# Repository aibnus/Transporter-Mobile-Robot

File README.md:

# Transporter-Mobile-Robot
Mobile Robot with ability to do Line Following, Wall Following, and Transporting any type of object with maximum diameter of 5cm.

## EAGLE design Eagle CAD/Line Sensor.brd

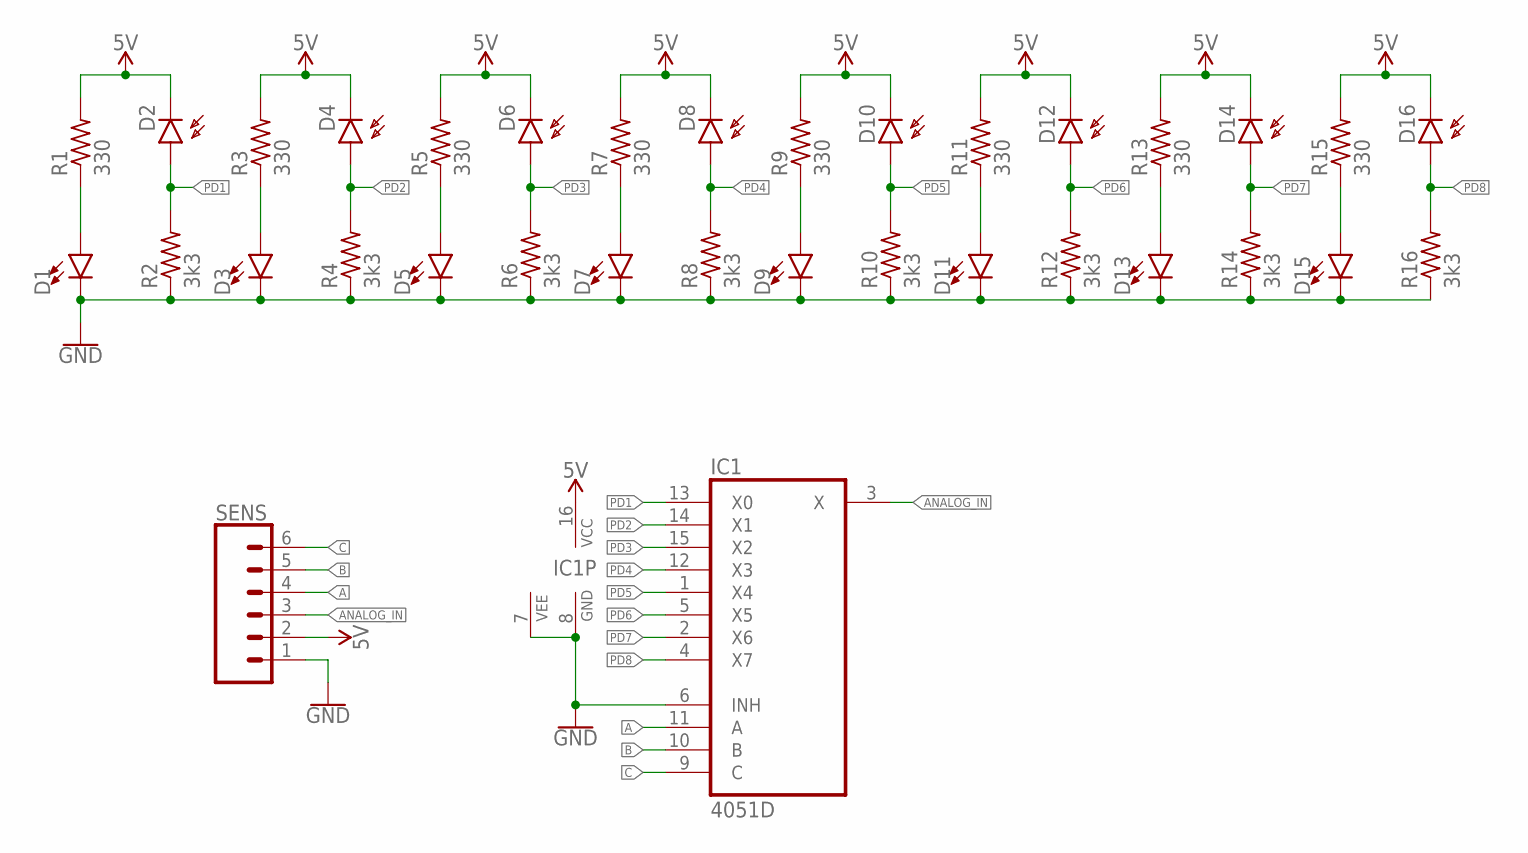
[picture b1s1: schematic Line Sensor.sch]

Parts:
D1, D3, D5, D7, D9, D11, D13, D15: LED3MM; LED_3MM
D2, D4, D6, D8, D10, D12, D14, D16: SFH225
IC1: 4051D; SO16
R1, R3, R5, R7, R9, R11, R13, R15: 330; 0207/9
R2, R4, R6, R8, R10, R12, R14, R16: 3k3; 0207/9
SENS: CONN_06SILK_FEMALE_PTH; 1X06

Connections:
5V: D2.K (C), D4.K (C), D6.K (C), D8.K (C), D10.K (C), D12.K (C), D14.K (C), D16.K (C), IC1.16 (VCC), R1.2, R3.2, R5.2, R7.2, R9.2, R11.2, R13.2, R15.2, SENS.2
A: IC1.11 (A), SENS.4
ANALOG_IN: IC1.3 (X), SENS.3
B: IC1.10 (B), SENS.5
C: IC1.9 (C), SENS.6
GND: D1.K (C), D3.K (C), D5.K (C), D7.K (C), D9.K (C), D11.K (C), D13.K (C), D15.K (C), IC1.6 (INH), IC1.7 (VEE), IC1.8 (GND), R2.1, R4.1, R6.1, R8.1, R10.1, R12.1, R14.1, R16.1, SENS.1
unnamed: D15.A, R15.1
unnamed: D13.A, R13.1
unnamed: D11.A, R11.1
unnamed: D9.A, R9.1
unnamed: D7.A, R7.1
unnamed: D5.A, R5.1
unnamed: D3.A, R3.1
unnamed: D1.A, R1.1
PD1: D2.A, IC1.13 (X0), R2.2
PD2: D4.A, IC1.14 (X1), R4.2
PD3: D6.A, IC1.15 (X2), R6.2
PD4: D8.A, IC1.12 (X3), R8.2
PD5: D10.A, IC1.1 (X4), R10.2
PD6: D12.A, IC1.5 (X5), R12.2
PD7: D14.A, IC1.2 (X6), R14.2
PD8: D16.A, IC1.4 (X7), R16.2

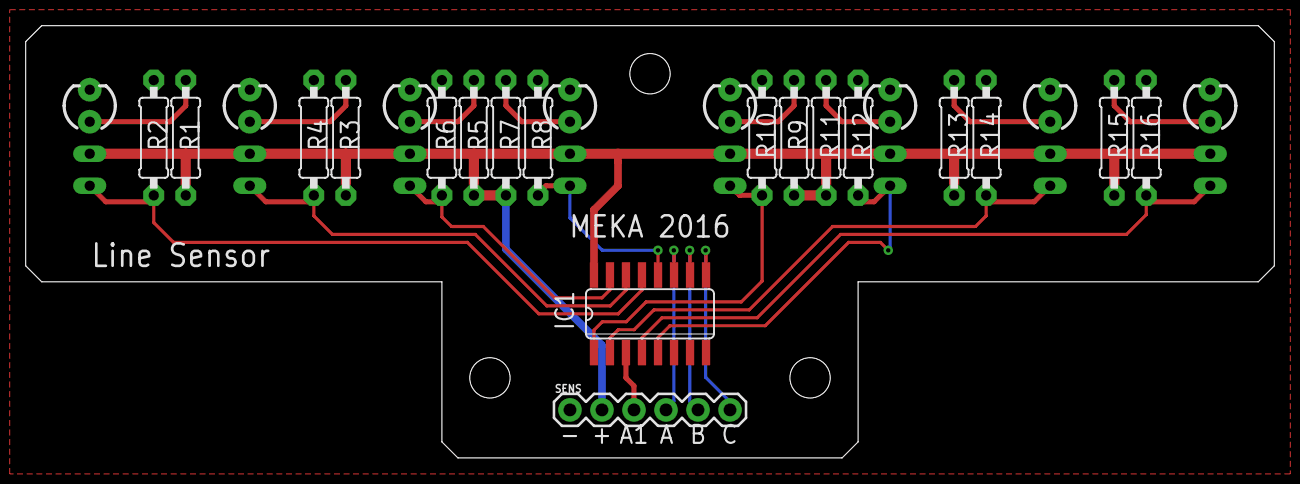
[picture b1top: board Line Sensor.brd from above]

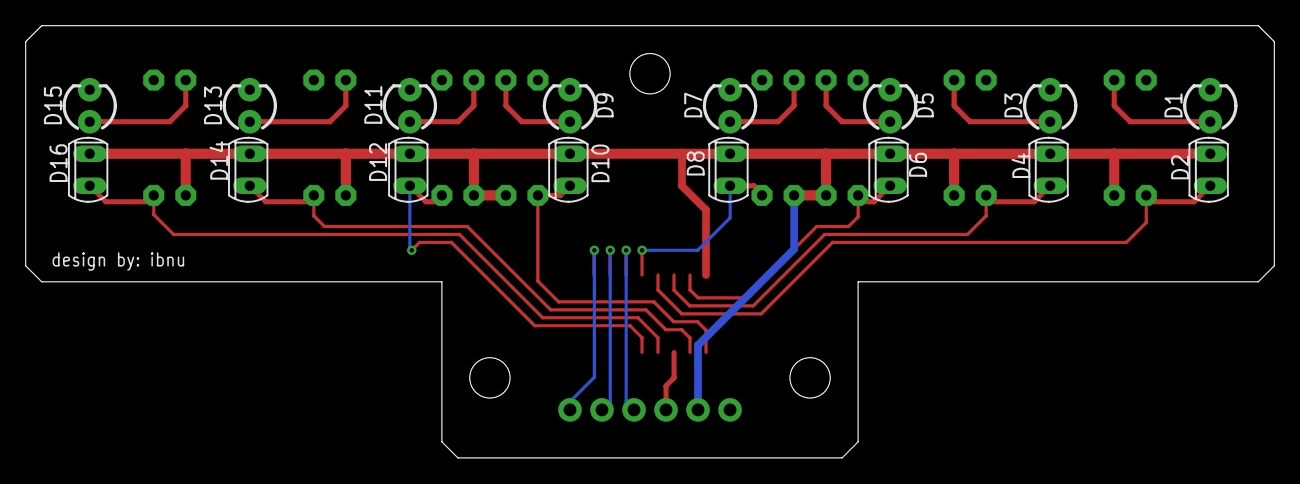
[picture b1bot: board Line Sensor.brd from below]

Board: 2 copper layers, 99.1 x 34.3 mm, 34 parts (16 on the bottom side), 22 nets.

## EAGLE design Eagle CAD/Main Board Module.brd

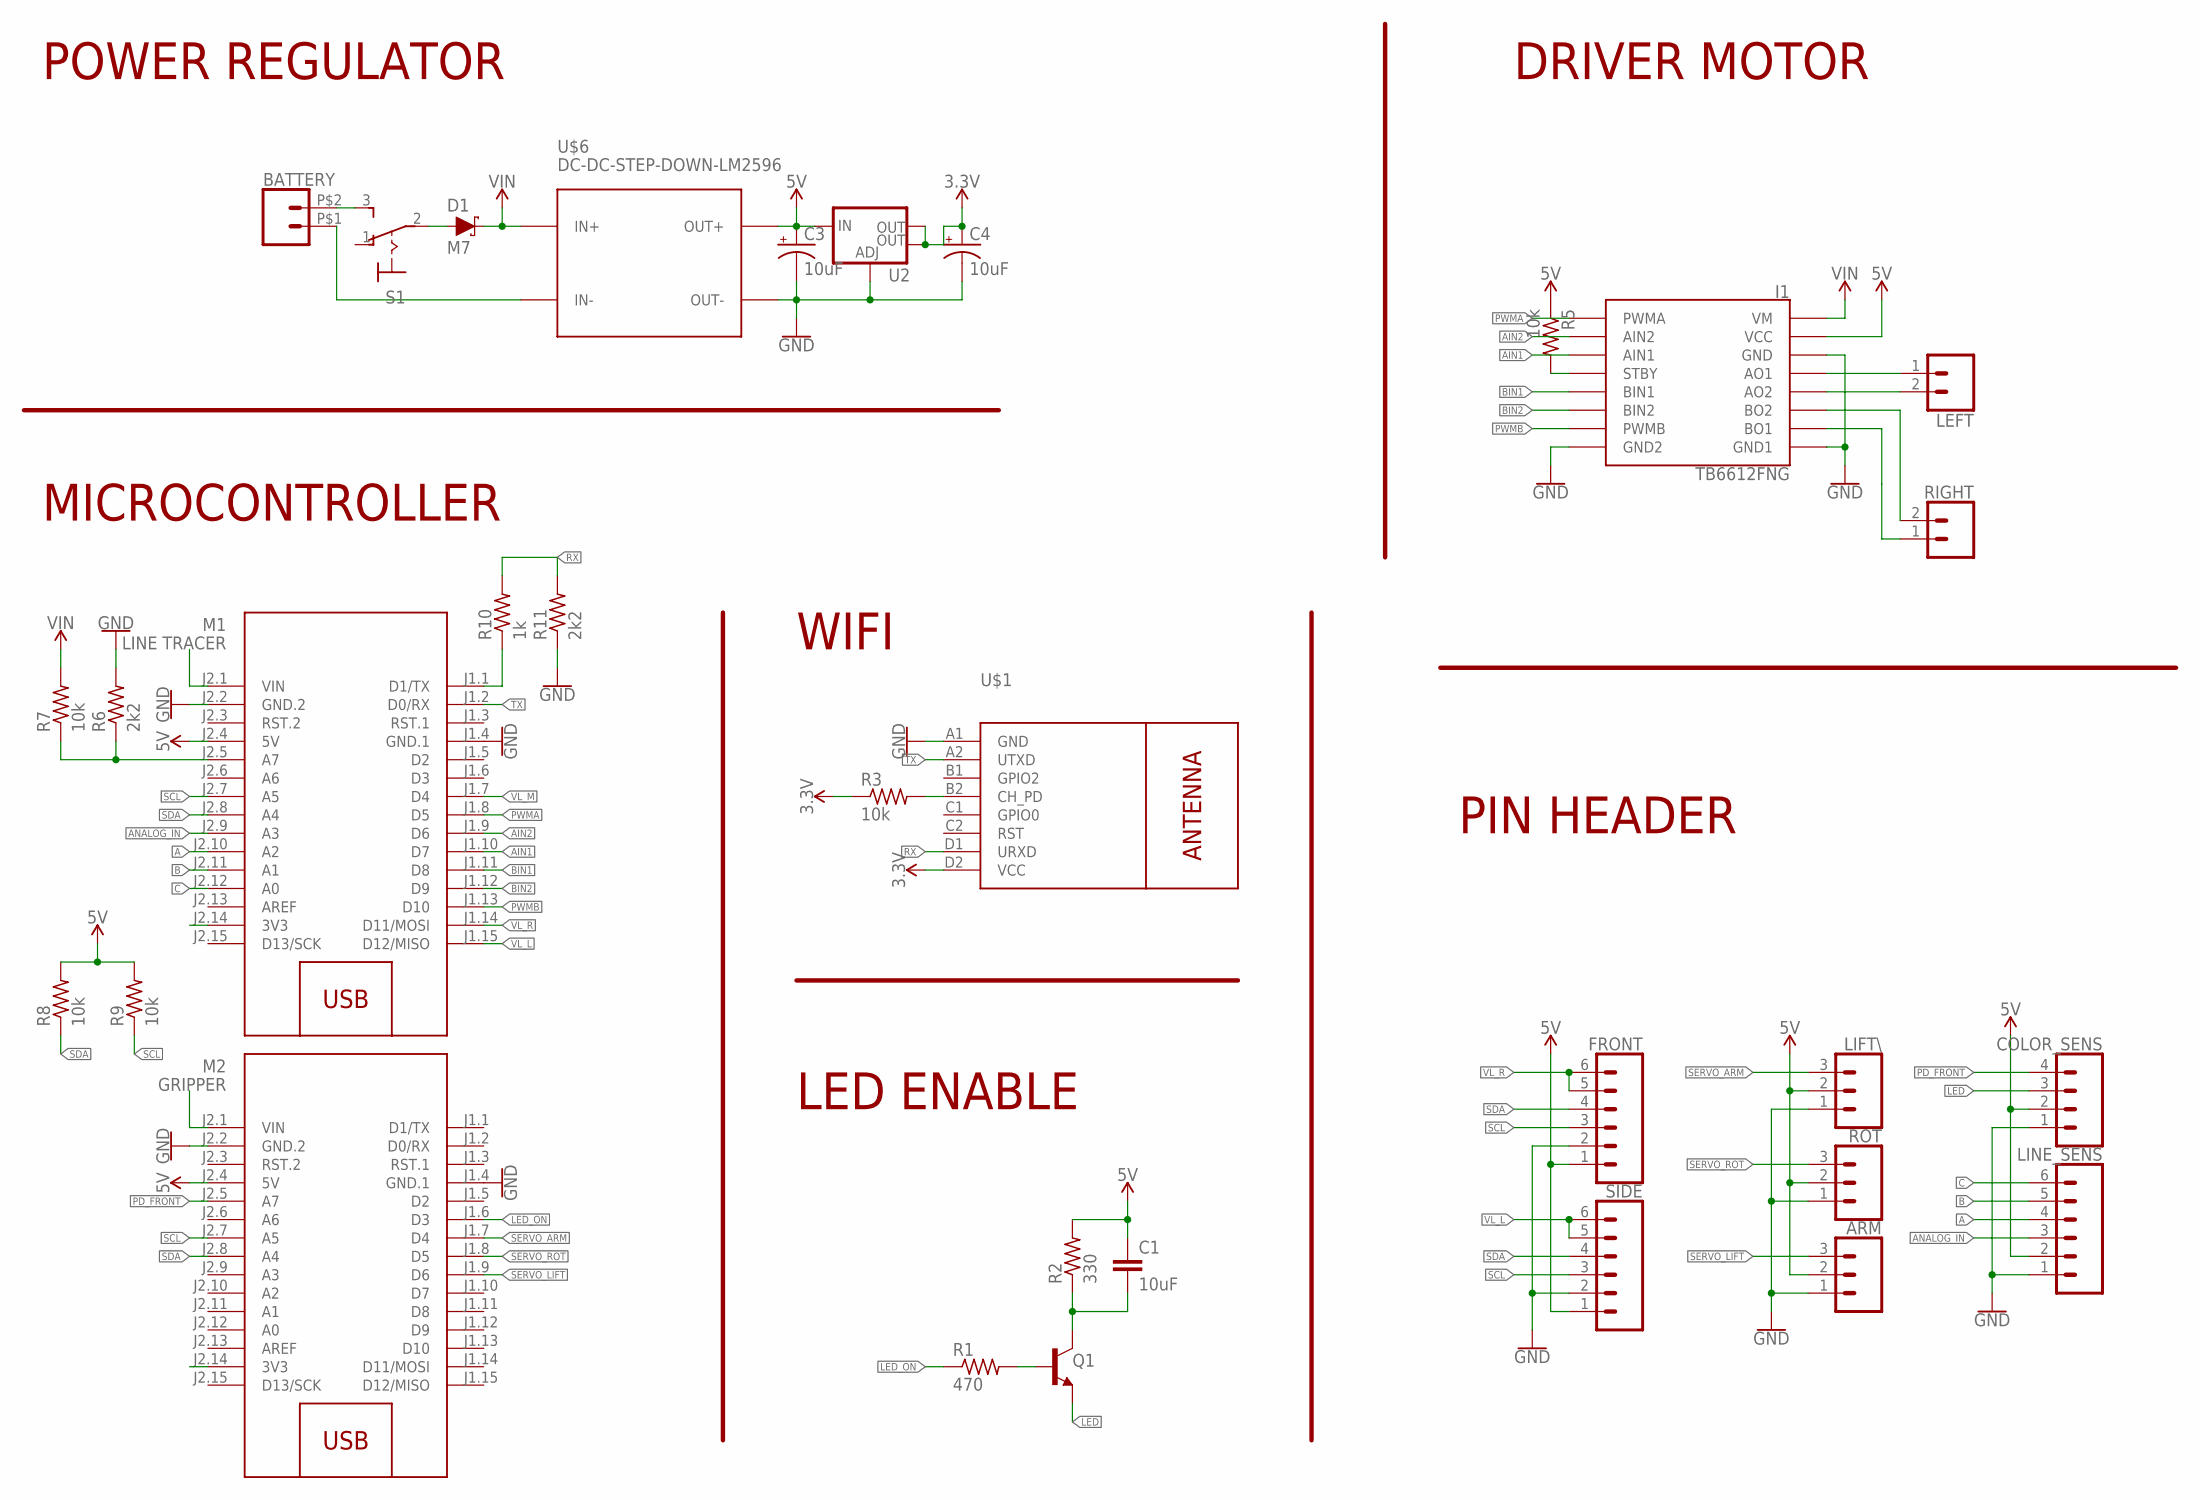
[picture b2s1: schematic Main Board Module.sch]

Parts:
ARM: CONN_03; 1X03
BATTERY: CONN_02PTH2; 1X02_BIG
C1: 10uF; C1206
C3, C4: 10uF; EIA3216
COLOR_SENS: CONN_04; 1X04
D1: M7; SMA-DIODE
FRONT: CONN_06SILK_FEMALE_PTH; 1X06
I1: TB6612FNG_MODULE; TB6612FNG
LEFT: CONN_02POLAR; MOLEX-1X2
LIFT\: CONN_03; 1X03
LINE_SENS: CONN_06SILK_FEMALE_PTH; 1X06
M1: LINE TRACER; ARDUINO-NANO-3.0
M2: GRIPPER; ARDUINO-NANO-3.0
Q1: TRANS_NPN-MMBT2222AL; SOT23-3
R1: 470; R1206
R2: 330; R1206
R3: 10k; R1206
R5, R7, R8, R9: 10k; 0207/9
R6, R11: 2k2; 0207/9
R10: 1k; 0207/9
RIGHT: CONN_02POLAR; MOLEX-1X2
ROT: CONN_03; 1X03
S1: 320-916
SIDE: CONN_06SILK_FEMALE_PTH; 1X06
U2: V_REG_LM1117SOT223; SOT223
U$1: WIRELESS-WIFI-ESP-01
U$6: DC-DC-STEP-DOWN-LM2596

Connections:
3.3V: C4.+, R3.1, U2.2 (OUT), U2.4 (OUT), U$1.D2 (VCC)
5V: ARM.2, C1.1, C3.+, COLOR_SENS.2, FRONT.1, I1.VCC, LIFT\.2, LINE_SENS.2, M1.J2.4 (5V), M2.J2.4 (5V), R2.2, R5.1, R8.2, R9.2, ROT.2, SIDE.1, U2.3 (IN), U$6.OUT+
A: LINE_SENS.4, M1.J2.10 (A2)
AIN1: I1.AIN1, M1.J1.10 (D7)
AIN2: I1.AIN2, M1.J1.9 (D6)
ANALOG_IN: LINE_SENS.3, M1.J2.9 (A3)
B: LINE_SENS.5, M1.J2.11 (A1)
BIN1: I1.BIN1, M1.J1.11 (D8)
BIN2: I1.BIN2, M1.J1.12 (D9)
C: LINE_SENS.6, M1.J2.12 (A0)
GND: ARM.1, C3.-, C4.-, COLOR_SENS.1, FRONT.2, I1.GND, I1.GND1, I1.GND2, LIFT\.1, LINE_SENS.1, M1.J1.4 (GND.1), M1.J2.2 (GND.2), M2.J1.4 (GND.1), M2.J2.2 (GND.2), R6.2, R11.1, ROT.1, SIDE.2, U2.1 (ADJ), U$1.A1 (GND), U$6.OUT-
LED: COLOR_SENS.3, Q1.2 (E)
LED_ON: M2.J1.6 (D3), R1.1
unnamed: Q1.1 (B), R1.2
unnamed: C1.2, Q1.3 (C), R2.1
unnamed: D1.A, S1.2
unnamed: BATTERY.P$2 (2), S1.3 (S)
unnamed: BATTERY.P$1 (1), U$6.IN-
unnamed: R3.2, U$1.B2 (CH_PD)
unnamed: I1.STBY, R5.2
unnamed: I1.AO1, LEFT.1
unnamed: M1.J2.5 (A7), R6.1, R7.1
unnamed: I1.AO2, LEFT.2
unnamed: I1.BO1, RIGHT.1
unnamed: M1.J1.1 (D1/TX), R10.1
unnamed: I1.BO2, RIGHT.2
PD_FRONT: COLOR_SENS.4, M2.J2.5 (A7)
PWMA: I1.PWMA, M1.J1.8 (D5)
PWMB: I1.PWMB, M1.J1.13 (D10)
RX: R10.2, R11.2, U$1.D1 (URXD)
SCL: FRONT.3, M1.J2.7 (A5), M2.J2.7 (A5), R9.1, SIDE.3
SDA: FRONT.4, M1.J2.8 (A4), M2.J2.8 (A4), R8.1, SIDE.4
SERVO_ARM: LIFT\.3, M2.J1.7 (D4)
SERVO_LIFT: ARM.3, M2.J1.9 (D6)
SERVO_ROT: M2.J1.8 (D5), ROT.3
TX: M1.J1.2 (D0/RX), U$1.A2 (UTXD)
VIN: D1.C, I1.VM, R7.2, U$6.IN+
VL_L: M1.J1.15 (D12/MISO), SIDE.5, SIDE.6
VL_M: M1.J1.7 (D4)
VL_R: FRONT.5, FRONT.6, M1.J1.14 (D11/MOSI)

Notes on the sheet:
POWER REGULATOR
MICROCONTROLLER
WIFI
LED ENABLE
DRIVER MOTOR
PIN HEADER

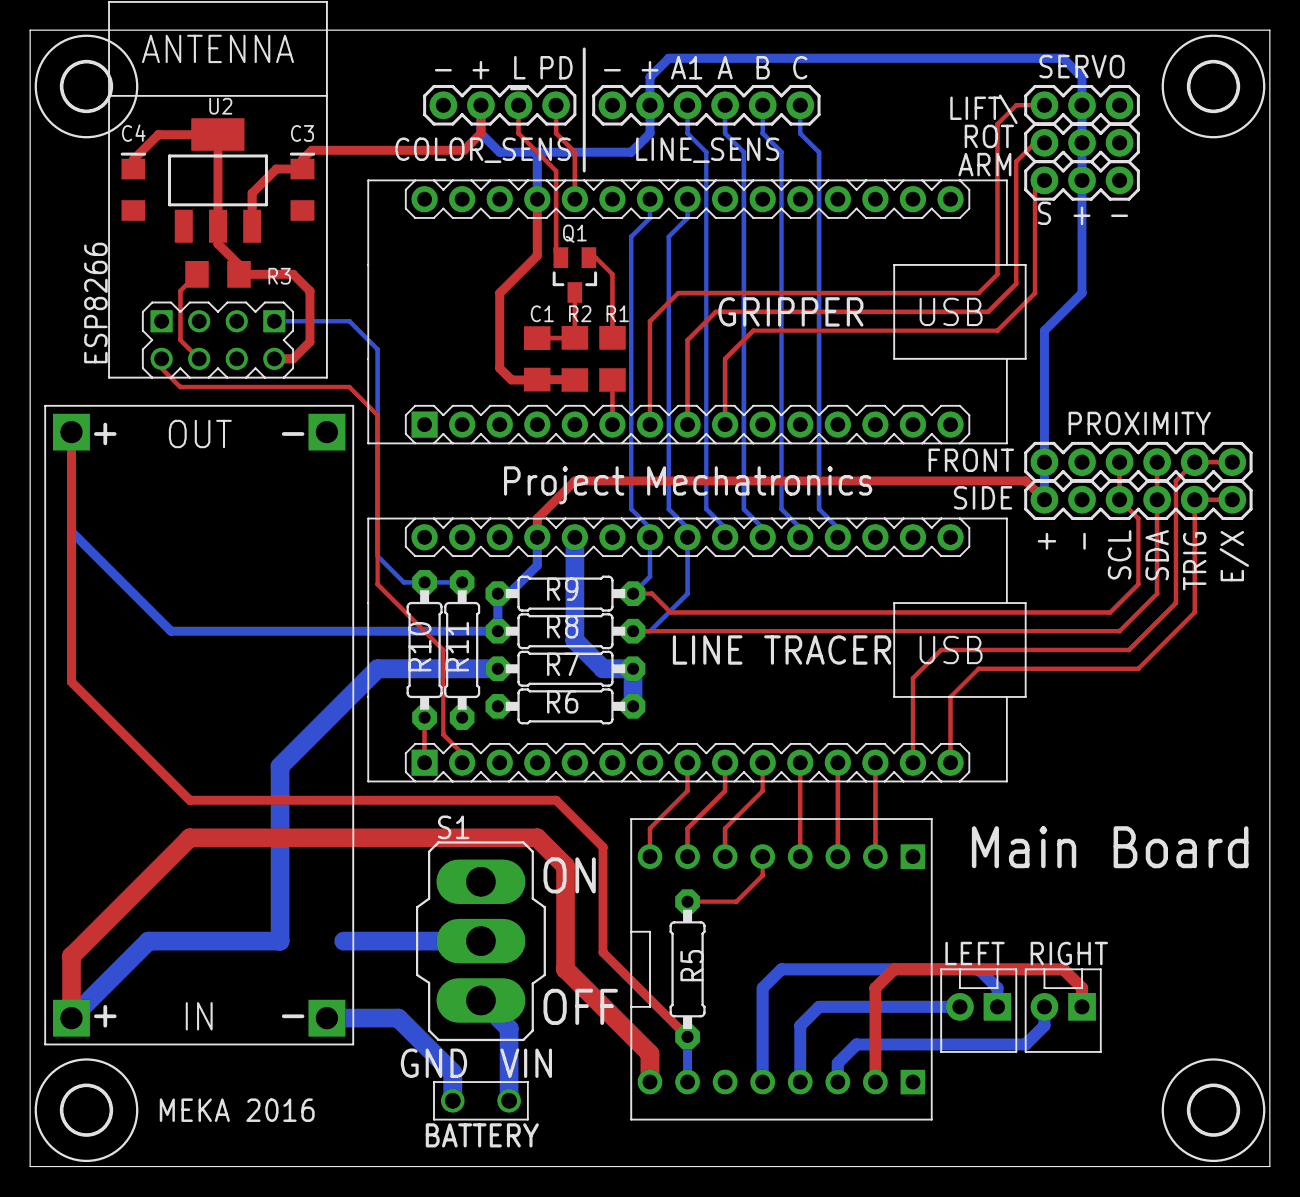
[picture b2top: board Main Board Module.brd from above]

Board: 2 copper layers, 83.8 x 76.8 mm, 36 parts (1 on the bottom side), 39 nets.

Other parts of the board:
U$2, U$3, U$4, U$5: 3,2

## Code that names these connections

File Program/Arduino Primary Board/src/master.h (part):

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//===== Driver Motor =====//
#include <SparkFun_TB6612.h>
//Define motor driver pin
#define PWMA 5
#define AIN2 6
#define AIN1 7
#define BIN1 8
#define BIN2 9
#define PWMB 10

//Make left and right motor object
Motor motorL(AIN1, AIN2, PWMA, 1, 0);
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

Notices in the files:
parts and their libraries:
SparkFun-LED: Licensing: Creative Commons ShareAlike 4.0 International - https://creativecommons.org/licenses/by-sa/4.0
diy-modules: Released under the Creative Commons Attribution 4.0 International License: http://creativecommons.org/licenses/by/4.0
